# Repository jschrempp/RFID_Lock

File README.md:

# RFID_Lock

Hardware and firmware for a Photon-based device that can control various locking mechanisms.

The device subscribes to publications with the name "checkin". These events are published by an RFID Station. 
The event data is JSON encoded and includes the deviceType of the publisher, as well as a secret security key.

Each lock station is configured via an App (or via the Particle Cloud) to act on a checkin event from a particular deviceType. 
If the event contains the correct deviceType and the correct secret key, then this device will unlock a cabinet, door, machine or power.

## Story
Our MN_ACL project (https://github.com/TeamPracticalProjects/MN_ACL) creates an infrastructure for secure, 
RFID-based access control to a Makerspace and it's various internal equipment locations.  That project integrates
Particle Argon-based RFID stations with a commercial cloud CRM system and an internal tracking database.
The MN_ACL project ensures that people who access the facility are paid up members in good standing and that
members who access certain locations containing sophisticated industrial equipment have basic operating 
and safety instruction credentials.  The project controls access via red/green lit buttons and an audible beeper.

Certain locations within the Makerspace contain expensive materials, parts and accessories.  We decided to create 
a Particle Photon-based add-on that could subscribe to publications sent by the Argons in the RFID stations
and unlock cabinets containing these expensive accessories.  We therefore needed to find an inexpensive but 
effective electrically controlled locking mechanism and create a Photon-based printed circuit board (and
associated Particle firmware) to unlock the cabinet when a member taps into one of the relevant RFID
stations with credentials that allow them access to these accessories.

COVID-19 related health and safety regulations require that the front door be locked to the outside and 
access to the facility be controlled. There is a 24 volt (DC) solenoid in the door mechanism that is wired 
back into the facility equipment room.  We determined that mounting an RFID station at the front entrance and 
using the same publish/subscribe mechanism as for cabinet locks, we could remotely and securely activate the front 
door solenoid lock to admit members when they tap their badge to the front door RFID station.

We decided to generalize this mechanism as much as possible in order to accommodate other access control requirements as
they arise in the future.

We decided that we needed a separate WiFi enabled circuit board for this purpose because:

1. The relationship between RFID stations and cabinets/locks is many to many.

2. Hardwiring a lock control signal from an RFID station to certain cabinets or locks is both inconvenient
and easily hacked.

3. A general-purpose, secure, WiFi enabled locking mechanism is a worthwhile and useful project
in and of itself, independent of the MN_ACL project and it's RFID stations.

We selected the Particle Photon for this project because it provides a low cost and secure means of WiFi
control and communication and because of Particle's simple and elegant cloud communication capabilities.

## Locking Mechanisms
### Locking a cabinet
We investigated a number of solutions for electrically controlled locking mechanisms and we ultimately
decided to hack an off-the-shelf mechanism from Tokatuker; see: 
https://www.amazon.com/Tokatuker-Electronic-Cabinet-Hidden-Drawer/dp/B075QF1VPR

The Tokatuker cabinet lock is a complete RFID solution in itself, but it does not have the required 
security or database integrations required for this project.  We therefore removed the electronics 
and provided our own Photon-based hardware to control the lock.  We also removed the batteries and 
we power the Tokatuker mechanism from our hardware so that the cabinets would not be stuck locked 
if a battery runs down.

We chose the Tokatuker solution because the locking mechanism itself is very innovative and uses only
a small, low power DC motor to control a mechanically robust locking system.  We found that pulsing this
motor for 30 milliseconds in one direction unlocks the lock and pulsing it for 30 milliseconds in the 
opposite direction re-locks the lock.  Unlocking the lock springs the cabinet door open and the door can
thereafter be closed and will lock anytime after the small motor returns to the locked position. The 
device can therefore unlock, opening the cabinet door, and then immediately re-lock and the door can 
be closed and will automatically lock at any time thereafter.

### The front door
The facility front door has a locking pushbar that includes a solenoid for remote unlocking.  This solenoid
was already wired back to the facility's equipment room. We experimentally determined that activating the 
solenoid for 2 seconds after a successful RFID card tap-in by a member in good standing is more than sufficient 
to provide entry to the facility.

### Our documentation
This project contains complete instructions for building an RFID Lock using the Tokatuker product.  This
project also contains instructions and firmware for activating a door-unlocking solenoid.
We also investigated various other locking mechanisms based upon servos, solenoids, etc.
We have included some information about these other approaches in this repository but we cannot
supply complete mechanics and Particle firmware to use them, as we did not carry these other locking
solutions through to a complete project solution.

## Electronics
We developed a printed circuit board that houses a Photon and integrates the Photon with components
that allowed us to test out various locking solutions.  This printed circuit board seemed so generally
useful to us that we have made it a project unto itself.  See: 
https://github.com/TeamPracticalProjects/Wireless_IO_Board

This project uses the Wireless_IO_Board hardware and we have added the Particle firmware necessary
to subscribe to publications from MN_ACL RFID Stations.  The documentation included with this project
provides ample references to these other projects where necessary.  Two sets of firmware are documented:
(1) firmware to respond to valid check-in events and unlock the modified Tokatuker motor lock.
(2) firmware to respond to valid check-in event and activate a door unlock solenoid.

## Mechanics
The modifications to the Tokatuker lock are documented in this repository.  Likewise, instructions
are provided for mounting the hardware in a small test cabinet that is demonstrative but also
useful in its own right.

## Firmware
This project includes Particle firmware (source code) for the Photon that integrates the RFID Lock
into the complete MN_ACL access control solution.

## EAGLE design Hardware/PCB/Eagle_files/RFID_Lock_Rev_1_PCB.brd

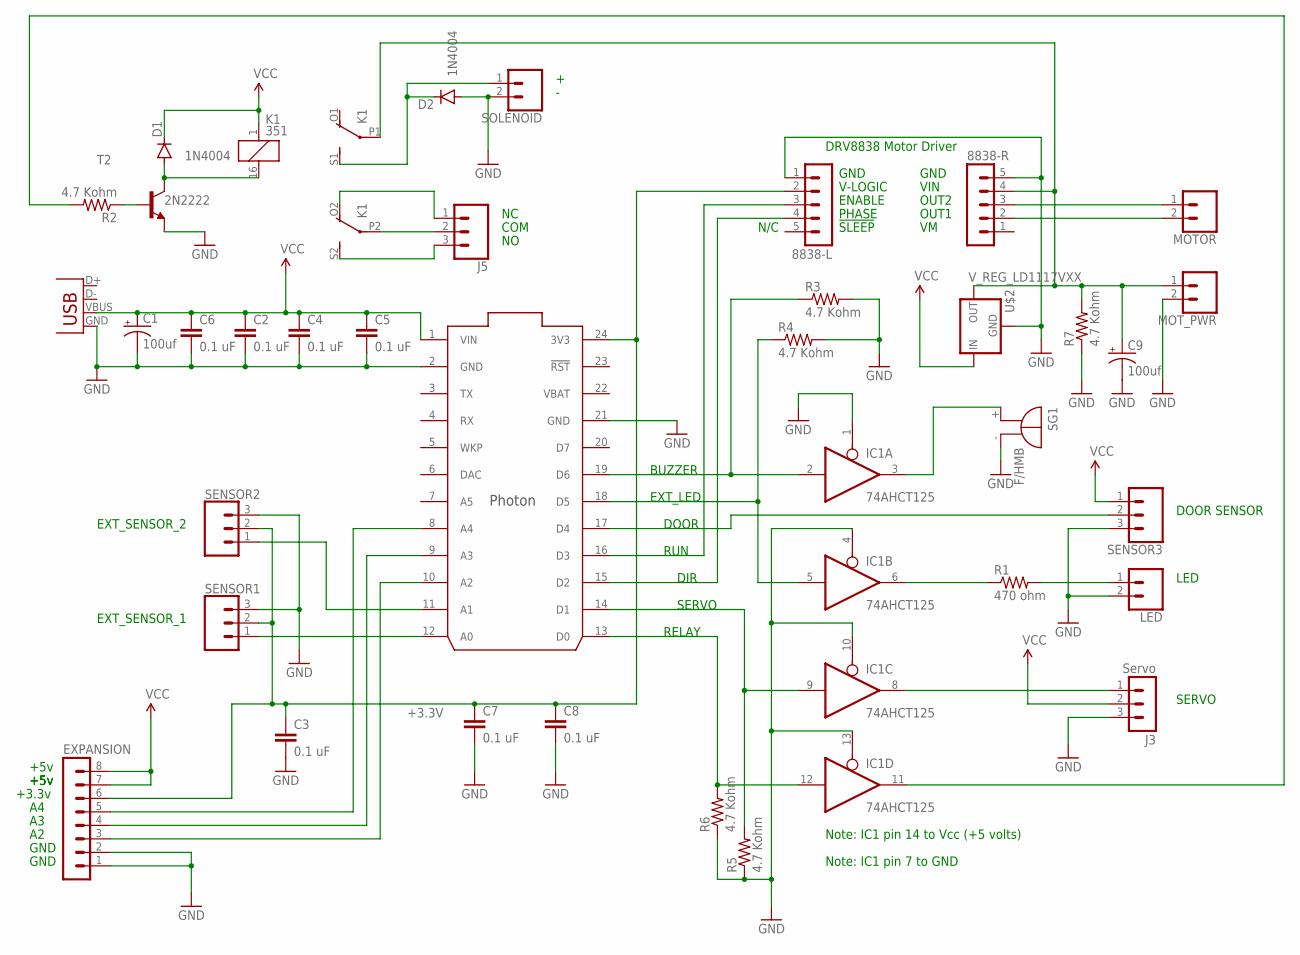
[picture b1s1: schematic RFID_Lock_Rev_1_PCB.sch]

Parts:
8838-L, 8838-R: MA05-1
C1, C9: 100uf; CPOL-RADIAL-100UF-25V
C2, C3, C4, C5, C6, C7, C8: 0.1 uF; CAP-PTH-SMALL
D1, D2: 1N4004; DO41-10
EXPANSION: MA08-1
IC1: 74AHCT125; DIL14
J3: Servo; MA03-1
J5: CONN_03SCREW; SCREWTERMINAL-3.5MM-3
JP1: USB-B; USB-B-PTH
K1: 351
LED: CONN_023.5MM; SCREWTERMINAL-3.5MM-2
MOTOR: CONN_023.5MM; SCREWTERMINAL-3.5MM-2
MOT_PWR: CONN_023.5MM; SCREWTERMINAL-3.5MM-2
R1: 470 ohm; 0309/12
R2, R3, R4, R5, R6, R7: 4.7 Kohm; 0309/12
SENSOR1, SENSOR2, SENSOR3: CONN_03SCREW; SCREWTERMINAL-3.5MM-3
SG1: F/HMB
SOLENOID: CONN_023.5MM; SCREWTERMINAL-3.5MM-2
T2: 2N2222; TO92-EBC-OVAL
U$1: PHOTON_WITH_HEADERS; PHOTON
U$2: V_REG_LD1117VXX; 78XXL

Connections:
+3.3V: 8838-L.2, C3.1, C7.1, C8.1, EXPANSION.6, SENSOR1.2, SENSOR2.2, U$1.24 (3V3)
GND: 8838-L.1, 8838-R.5, C1.2 (-), C2.2, C3.2, C4.2, C5.2, C6.2, C7.2, C8.2, C9.2 (-), D2.A, EXPANSION.1, EXPANSION.2, IC1.1 (OE), IC1.4 (OE), IC1.7 (GND), IC1.10 (OE), IC1.13 (OE), J3.3, JP1.GND, LED.2, MOT_PWR.2, R3.2, R4.2, R5.1, R6.1, R7.1, SENSOR1.3, SENSOR2.3, SENSOR3.3, SG1.-, SOLENOID.2, T2.E, U$1.2 (GND), U$1.21 (GND), U$2.IN (GND)
unnamed: IC1.8 (O), J3.1
unnamed: SENSOR2.1, U$1.11 (A1)
unnamed: SENSOR1.1, U$1.12 (A0)
unnamed: IC1.2 (I), R3.1, U$1.19 (D6)
unnamed: 8838-L.3, U$1.16 (D3)
unnamed: IC1.3 (O), SG1.+
unnamed: IC1.9 (I), R5.2, U$1.14 (D1)
unnamed: 8838-R.3, MOTOR.1
unnamed: IC1.6 (O), R1.1
unnamed: LED.1, R1.2
unnamed: SENSOR3.2, U$1.17 (D4)
unnamed: 8838-L.4, U$1.15 (D2)
unnamed: 8838-R.2, MOTOR.2
unnamed: EXPANSION.3, U$1.10 (A2)
unnamed: EXPANSION.4, U$1.9 (A3)
unnamed: IC1.12 (I), R6.2, U$1.13 (D0)
unnamed: EXPANSION.5, U$1.8 (A4)
unnamed: IC1.11 (O), R2.2
unnamed: R2.1, T2.B
unnamed: D1.A, K1.16 (2), T2.C
unnamed: D2.C, K1.S1 (S), SOLENOID.1
unnamed: IC1.5 (I), R4.1, U$1.18 (D5)
unnamed: 8838-R.4, C9.1 (+), K1.P1, MOT_PWR.1, R7.2, U$2.GND (OUT)
unnamed: J5.2, K1.P2
unnamed: J5.1, K1.O2 (O)
unnamed: J5.3, K1.S2 (S)
VBAT: U$1.22 (VBAT)
VCC: C1.1 (+), C2.1, C4.1, C5.1, C6.1, D1.C, EXPANSION.7, EXPANSION.8, IC1.14 (VCC), J3.2, JP1.VBUS, K1.1, SENSOR3.1, U$1.1 (VIN), U$2.OUT (IN)

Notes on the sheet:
EXT_SENSOR_1
SERVO
Note: IC1 pin 14 to Vcc (+5 volts)
Note: IC1 pin 7 to GND
DOOR SENSOR
LED
+5v
+3.3v
GND
V-LOGIC
ENABLE
PHASE
!SLEEP
VIN
OUT2
OUT1
N/C
DRV8838 Motor Driver
DIR
RUN
RELAY
BUZZER
DOOR
EXT_LED
EXT_SENSOR_2
COM

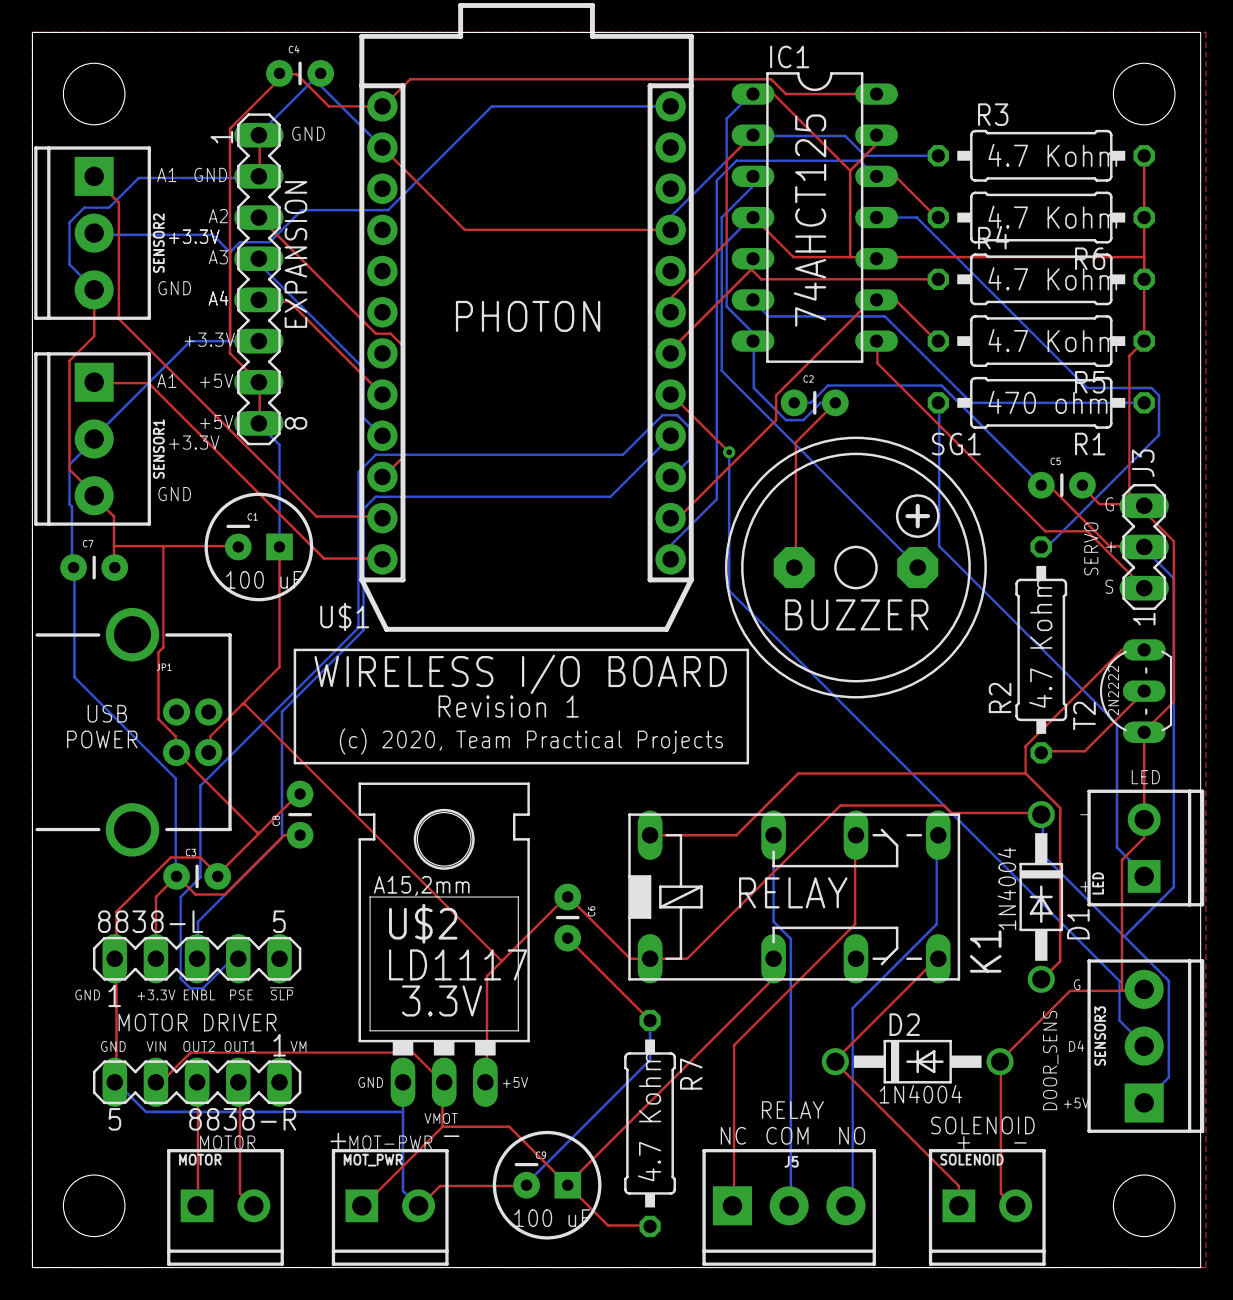
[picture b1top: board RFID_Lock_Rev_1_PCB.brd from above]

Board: 2 copper layers, 72.1 x 76.2 mm, 37 parts (0 on the bottom side), 29 nets.

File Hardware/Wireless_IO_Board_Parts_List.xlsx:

LOCATION | ITEM | Part Number | Qty | Description | Vendor | URL | Unit Price | Total price | NOTES | ALT Supplier
PCB | 1 | 1536 | 1 | Piezo Buzzer - 5 volt | Adafruit | https://www.adafruit.com/product/1536 | 0.95 | 0.95
PCB | 2 | 1030 | 2 | Headers for Photon | Pololu | https://www.pololu.com/product/1030 | 0.79 | 1.58
PCB | 3 | 392 | 1 | Male pin headers, 40 pin, breakaway | Pololu | https://www.pololu.com/category/134/0.1-2.54-mm-male-headers | 0.75 | 0.75
PCB | 4 | 2781 | 10 | Resistor, 470 ohm | Jameco | https://www.jameco.com/z/CF1-4W471JRC-Resistor-Carbon-Film-4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 | 0.06 | 0.6 | Need 1 resistor; minimum order is 10
PCB | 5 | 691024 | 10 | Resistor, 4.7 Kohm | Jameco | https://www.jameco.com/z/CF1-4W472JRC-Resistor-Carbon-Film-4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 | 0.06 | 0.6 | Need 7 resistors; minimum order is 10
PCB | 6 | 1787 | 1 | 74AHCT125 quad level shifter | Adafruit | https://www.adafruit.com/product/1787 | 1.5 | 1.5
PCB | 7 | 112214 | 1 | IC socket, 14 pin DIP, 0.3" | Jameco | https://www.jameco.com/z/6000-14DW-R-Socket-IC-14-Pin-Dual-W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 | 0.25 | 0.25
PCB | 8 | Photon | 1 | Particle Photon, with headers | Particle | https://store.particle.io/collections/wifi/products/photon | 19 | 19
PCB | 9 | 2842 | 1 | motor driver based on DRV8838 | Pololu | https://www.pololu.com/product/2990 | 3.49 | 3.49
PCB | 10 | 2990 | 1 | power regulator, 5 volt in to 3.3 volt out | Pololu | https://www.pololu.com/product/2842 | 4.95 | 4.95
PCB | 11 | 544921 | 7 | Capacitor, 0.1 uF; 10 pack | Jameco | https://www.jameco.com/shop/ProductDisplay?catalogId=10001&l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 | 0.25 | 1.75
PCB | 12 | 29891 | 2 | Capacitor, radial, 100 uF | Jameco | https://www.jameco.com/z/RB100-10-Capacitor-Radial-100-uF-10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 | 0.25 | 0.5
PCB | 13 | PCB | 1 | Printed circuit board | jlcpcb | https://jlcpcb.com | 2 | 2 | $2.00 for 5 boards, plus shipping. Upload the Eagle CAM .zip file to this web s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
PCB | 14 | 35991 | 2 | diode, 1N4004 | Jameco | https://www.jameco.com/z/1N4004-Major-Brands-Diode-1N4004-40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 | 0.25 | 0.5
PCB | 15 | 787536 | 1 | transistor, 2N2222A; TO-92 package | Jameco | https://www.jameco.com/z/PN2222ATRA-Fairchild-Semiconductor-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 | 0.39 | 0.39
PCB | 16 |  | 1 | relay, 5 volt - 150 ohm, DPDT |  | https://www.jameco.com/shop/ProductDisplay?catalogId=10001&l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 | 2.99 | 2.99
PCB | 17 | 1014 | 2 | female pin header, 0.1", 4 position | Pololu | https://www.pololu.com/product/1014 | 0.39 | 0.78 | need 1; minimum order is 2
PCB | 18 | 1015 | 2 | female pin header, 0.1", 5 position | Pololu | https://www.pololu.com/product/1015 | 0.44 | 0.88
PCB | 19 | 2094506 | 5 | PCB terminal block, 3.5 mm, 2 position | Jameco | https://www.jameco.com/webapp/wcs/stores/servlet/ProductDisp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 | 0.49 | 2.4500000000000002
PCB | 20 | 2094514 | 3 | PCB terminal block, 3.5 mm, 3 position | Jameco | https://www.jameco.com/webapp/wcs/stores/servlet/ProductDisp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 | 0.79 | 2.37
PCB | 21 | 230958 | 1 | PCB USB connector, type B female | Jameco | https://www.jameco.com/z/USB-B-S-RA-CS1-SPCC-WT-Adam-Technol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 | 0.79 | 0.79
S/T PCB: |  |  |  |  |  |  |  | 38.42
LOCK | 1 |  |  |  |  |  |  | 0
S/T Lock: |  |  |  |  |  |  |  | 0
TOTAL: |  |  |  |  |  |  |  | 38.42

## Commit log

2020-03-14 Populate Repository
    Initial population of reposiitory with information from tested breadboard
2020-03-14 Cleaned up hardware folder
2020-03-15 Consolidated firmware
    Consolidated firmware for servo, motor and I/O locks into one test routine. Deleted the previous standalone servo_lock routine. The new consolidated routine has the correct pin definitions per the Ea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
2020-03-15 Updated schematic
    Updated board schematic to wire one relay pole to support a solenoid. The second relay pole is left for general purpose use.
2020-03-15 Placed parts on PCB
2020-03-16 Corrected PCB
    Corrected pin header spacing for motor driver.
2020-03-16 Update RFID_Lock_PCB.brd
    Added mounting holes to PCB
2020-03-16 Update RFID_Lock_PCB.brd
    Autorouted and copper poured the .brd file. Passes DRC.
2020-03-17 Update locktest.ino
    Added lock() before unlock() when activating the lock mechanism; emperically needed to work.
2020-03-18 Update locktest.ino
    Added 20 ms delay between lock() and unlock() to allow for the motor to settle down.
2020-03-18 Finalized Board File
    Added necessary silkscreen and created gerber files.
2020-03-19 Update locktest.ino
    Put in comments about possibly unneeded extra lock() and delay() commands, as I suspect that we damaged the test unit mechanically when we took it apart and tried to put it back together. Comment out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
2020-03-28 Update locktest.ino
    Removed the extra lock() commanda to the motor lock to test with the new factory fresh locking mechanism.
2020-04-02 Create Tokatuker_Cabinet_Digital_Lock_Testing.pdf
    Report on testing, inspection and controller design for the Tokatuker RFID cabinet lock unit modified for control via this project.
2020-04-02 Update Tokatuker_Cabinet_Digital_Lock_Testing.pdf
    Corrected pdf to include photos from the original document.
2020-04-09 Create PCB_Issues_For_Rework.txt
    Added a text file tracking the issues for rework of the PCB (to Rev 1).
2020-04-14 Update PCB_Issues_For_Rework.txt
    Updated with LD1117-3.3 voltage regulator and clarification about not needing R7 and R8.
2020-05-11 Updated PCB Files
    Updated PCB files to Rev 1. Also updated data sheets and misc information, but the parts list is NOT updated in this commit.
2020-05-13 Moved files to new repo
    Moved files to new Wireless_IO_Board repo. This repo will be dedicated to the use of the Wireless I/O board for controlling various cabinet locks.
2020-05-13 Added lock-specifc data files
2020-06-04 Created Readme,md file
2020-06-04 Added photos and reorganized
    Just raw material here - needs cleanup and some explanation.
2020-06-04 v0.1 works, but does a panic as soon as the unlock is over
2020-06-04 removed 6 calls to write to LCD
2020-06-05 0.2 it now works
2020-06-06 added cloud function to trip the lock
2020-06-13 updated settings
2020-06-29 Update README.md
    Minor corrections.
2020-06-30 Updated Testing Doc and rearranged repo
2020-06-30 Placeholders for Overview and Build docs
2020-07-01 Completed draft overview doc
2020-07-02 Update RFID_Lock_Project_Overview.pdf
    Incorporated Jim's suggestions
2020-07-05 Added build instructions and updated Readme.md
2020-07-10 Update RFID_Lock_Build_Instructions.pdf
    Added photos for mounting the pcb and the finished assembly.
2020-07-10 Update RFID_Lock_Build_Instructions.pdf
    Incorporated Jim's comments
2020-08-09 solenoid firmware v0.1
2020-08-19 0.2 checkin event must have secret code
2020-08-20 v0.3 production compile directive
2020-08-20 adding workspace and gitignore
2020-08-20 removed vscode settings file
2020-08-20 removed particle readme
2020-08-22 v0.3 added validate checkin event
2020-08-22 added validate checkin event
2020-08-22 gitignore update
2020-08-22 added MN_PRODUCTION define
2020-08-28 Updates for Solenoid Lock
    Updated READme.md and Project Overview document to include the front door solenoid. Still need to work on build instructions and other HW documentation.
2020-08-30 Added build instructions for solenoid lock
    Added these instructions and updated the overview document to include this build instruction doc in its repo description.
2020-08-30 Update RFID_Lock_Project_Overview.pdf
    Corrected typos
2020-08-31 Update Solenoid_Lock_Build_Instructions.pdf
    Updated document with better photo of finshed project.
2020-09-03 Small update to add section heads
2021-04-26 0.4 added #define to disable debugX events
2021-04-26 removed lockbox.cpp
2021-04-26 v0.4 #define to prevent debugX events (untested)
2021-08-30 added antenna auto select
2021-09-07 solenoid hold time set to 4 seconds
2024-04-13 Update lockbox.code-workspace

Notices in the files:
Hardware/PCB/Eagle_files/RFID_Lock_Rev_1_PCB.brd:
(c) 2020, Team Practical Projects
parts and their libraries:
SparkFun-Capacitors: Licensing: CC v3.0 Share-Alike You are welcome to use this library for commercial purposes.
SparkFun-Passives: Licensing: Creative Commons ShareAlike 4.0 International - https://creativecommons.org/licenses/by-sa/4.0
